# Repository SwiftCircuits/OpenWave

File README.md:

# OpenWave: Precision Arbitrary Waveform Generator

<div align="center">

**A dual-channel, high-precision waveform generator designed for control system analysis and system identification**

[Features](#features) • [Getting Started](#getting-started) • [Documentation](#documentation) • [Contributing](#contributing)

</div>

## Why OpenWave?

Traditional arbitrary waveform generators often force a choice between expensive lab equipment or limited-capability hobby projects. OpenWave bridges this gap by providing professional-grade precision in an open-source design that prioritizes signal quality over raw speed. By focusing on the critical frequency range used in control systems and system identification (up to 500 kHz), we've optimized for exceptional signal quality and reliability.

### Key Features

- Dual independent channels with 16-bit resolution
- Optimized 500 kHz bandwidth with 80 dB SNR
- Sophisticated triggering system for precise control
- Multiple interface options: USB, Ethernet, and CAN
- Intuitive front panel control with LCD display
- Expansion capability through daughter board interface
- Precision temperature-monitored reference system
- Professional-grade signal filtering and conditioning

### Perfect For

- Control system development and testing
- System identification experiments
- Precision measurement applications
- Educational laboratory setups
- Research and development projects
- Industrial control system integration
- Signal processing development

## Technical Overview

OpenWave combines meticulous hardware design with flexible software to achieve exceptional signal quality:

### Signal Generation
- Dual 16-bit DACs (LTC2642-16) operating at 50 MSPS
- Third-order Sallen-Key filtering with Butterworth response
- Additional output stage conditioning
- Ultra-low noise power supply design
- Temperature-compensated reference system
- Comprehensive signal isolation and protection

### Control and Interface
- High-speed USB 2.0 interface
- 10/100 Ethernet connectivity
- Industrial-grade CAN interface
- Advanced trigger system with multiple modes:
  - Start trigger with precise timing
  - Level-sensitive pause control
  - Configurable burst mode
  - Status and peak detection outputs
- Intuitive front panel interface with LCD display

### Power System
- 12V DC input with protection
- Sophisticated multi-stage power architecture:
  - High-efficiency 5.5V pre-regulation
  - Ultra-low noise 5V analog supply
  - Clean 3.3V digital rail
  - Precision 3.3V reference
- Extensive power filtering and isolation

## Getting Started

### Current Status
This project is under active development. Current focus areas:
- Finalizing PCB layout and power distribution
- Implementing core firmware features
- Developing user interface systems
- Creating comprehensive documentation
- Establishing test procedures

### For Contributors

We welcome contributions in several areas:

**Hardware Development**
- PCB layout optimization
- Signal integrity improvements
- Power distribution refinement
- Manufacturing optimization
- Test coverage enhancement

**Firmware Development**
- STM32 core implementation
- Front panel interface development
- Communication protocol implementation
- Signal generation algorithms
- User interface refinement

**Documentation and Testing**
- System specification documentation
- Assembly and calibration procedures
- Performance verification methods
- Application examples
- User manual development

## Building OpenWave

### Hardware Requirements
- 4-layer PCB manufacturing capability
- SMD assembly equipment
- Precision test equipment:
  - Oscilloscope (>100MHz bandwidth)
  - Precision multimeter
  - Signal analyzer (recommended)
- STM32 programming capability
- Basic electronic assembly tools

### Software Requirements
- STM32CubeIDE development environment
- ARM GCC toolchain
- KiCad 7.0 or later
- Git version control
- Build system requirements (detailed in documentation)

## Documentation

> 🚧 Documentation is currently under development

Comprehensive documentation will cover:
- Complete system architecture
- Detailed theory of operation
- Assembly and testing procedures
- Calibration methodology
- Performance optimization
- Application examples
- Development guidelines

## Contributing

Your expertise can help make OpenWave better! Here's how you can contribute:

1. **Join Discussions**
   - Share your application requirements
   - Suggest performance improvements
   - Help define future features
   - Participate in design reviews

2. **Technical Contributions**
   - PCB design optimization
   - Firmware development
   - Documentation creation
   - Test procedure development
   - Performance validation

3. **Testing and Validation**
   - Prototype building and testing
   - Performance verification
   - Use case validation
   - Issue reporting and tracking

## Project Structure

```
/hardware           - KiCad design files
  /main            - Main board design
  /front_panel     - Front panel PCB
  /daughter_boards - Expansion board designs
  /manufacturing   - Production files
/firmware          - Source code
  /core            - Core STM32H7 functionality
  /front_panel     - STM32G0 interface code
  /libraries       - Shared libraries
  /tests           - Test suites
/docs              - Documentation
  /hardware        - Hardware documentation
  /firmware        - Software documentation
  /user            - User guides
  /testing         - Test procedures
```

## License

- Hardware: [CERN Open Hardware License Version 2](LICENSE-HARDWARE)
- Software: [MIT License](LICENSE-SOFTWARE)

## Acknowledgments

OpenWave builds on the work of many open-source projects and individuals. Special thanks to:
- The open hardware community for inspiration and shared knowledge
- Contributors who have helped shape the project's direction

## Contact and Support

- Create an issue for bugs or feature requests
- Join our discussions for general questions
- Email for other inquiries: constantinescu.alex02@gmail.com

---

<div align="center">

**[Back to Top](#openwave-precision-arbitrary-waveform-generator)**

</div>

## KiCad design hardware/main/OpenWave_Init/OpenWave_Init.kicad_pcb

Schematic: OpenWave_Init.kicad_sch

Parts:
BT1: Battery_Cell; Battery_Panasonic_CR1220-VCN_Vertical_CircularHoles
C1, C16, C19, C28: 1uF; C_0402; Voltage Rated 25V; Tolerance ±10%; Part CL05A105KA5NQNC; LCSC C52923
C2, C3, C4, C5, C6, C11, C15, C27, C29, C30, C31, C37, C38, C48, C55, C56, C57, C58, C59: 100nF; C_0402; Voltage Rated 50V; Tolerance ±10%; Part CL05B104KB54PNC; LCSC C307331
C7, C34: 10uF; C_CASE-A-3216-18(mm); Tolerance ±10%; Rated Voltage 16V; Part TAJA106K016RNJ; LCSC C7171
C8, C9: 10pF; C_0402; Voltage Rated 50V; Tolerance ±5%; Part CL05C100JB5NNNC; LCSC C32949
C10, C36: 2.2uF; C_0603; Voltage Rated 16V; Tolerance ±10%; Part CL10A225KO8NNNC; LCSC C23630
C12, C13, C14, C20, C35, C39, C54, C62: 10uF; C_0603; Voltage Rated 25V; Tolerance ±20%; Part CL10A106MA8NRNC; LCSC C96446
C17, C18, C21: 22uF; C_0805; Voltage Rated 25V; Tolerance ±20%; Part CL21A226MAQNNNE; LCSC C45783
C22, C23, C64: 4.7uF; C_0603; Voltage Rated 16V; Tolerance ±10%; Part CL10A475KO8NNNC; LCSC C19666
C24, C25, C26, C42, C46: 100pF; C_0402; Voltage Rated 50V; Tolerance ±5%; Part 0402CG101J500NT; LCSC C1546
C32, C33, C51, C63: 10nF; C_0402; Voltage Rated 50V; Tolerance ±10%; Part CL05B103KB5NNNC; LCSC C15195
C40, C47: 220nF; C_0402; Voltage Rated 16V; Tolerance ±10%; Part CL05B224KO5NNNC; LCSC C16772
C41, C45: 1.5nF; C_0603; Voltage Rated 50V; Tolerance ±10%; Part 0603B152K500NT; LCSC C1595
C43, C44: 680pF; C_0402; Voltage Rated 50V; Tolerance ±5%; Part 0402CG101J500NT
C49, C50: 6.8pF; C_0402; Voltage Rated 50V; Part 0402CG6R8C500NT; LCSC C1576
C52, C53: 15pF; C_0402; Voltage Rated 50V; Tolerance ±5%; Part 0402CG150J500NT; LCSC C1548
D1: LED; LED_0603_1608Metric
D2: SMAJ10CA; D_SMA; Part SMAJ10CA; LCSC C19077530
D3, D4, D5, D6, D7: TPRCLAMP2451ZA; D_DFN0603-2; Part TPRCLAMP2451ZA; LCSC C2936988
FB1, FB2, FB3, FB4, FB5, FB7: FB_0603; Current Rating 200mA; Tolerance ±25%; Part GZ1608D601TF; LCSC C1002
FB6: FB_0805; Current Rating 800mA; Tolerance ±25%; Part GZ2012D101TF; LCSC C1015
FL1: ACT1210D-101-2P-TL00; ACT1210D1012PTL00
FL2: Choke_Coilcraft_0603USB-222; L_CommonModeChoke_Coilcraft_0603USB
H1, H2, H3, H4: Hole, 3mm
IC1: TPS7A2050PDBVR; SOT95P280X145-5N; Mouser Part Number 595-TPS7A2050PDBVR
J1: UART; PinHeader_1x02_P2.54mm_Vertical
J2: SWD; PinHeader_2x03_P1.00mm_Vertical
J3: FPC 6S; Hirose_FH12-6S-0.5SH_1x06-1MP_P0.50mm_Horizontal
J4: Barrel_Jack_Switch_MountingPin; PRT10811
J5: Control_In; JST_XH_S2B-XH-A-1_1x02_P2.50mm_Horizontal
J6, J7: BNC; 5415025-2
J8: USB_C_Receptacle_USB2.0_16P; USB_C_Receptacle_GCT_USB4105-xx-A_16P_TopMnt_Horizontal
J9: RB1-125BAG1A; RB1125BAG1A; Mouser Part Number 950-RB1-125BAG1A
JP1: SolderJumper; SolderJumper-2_P1.3mm_Bridged2Bar_Pad1.0x1.5mm
JP2: Termination Jumper; SolderJumper-2_P1.3mm_Open_Pad1.0x1.5mm
L1: 22uH, 340mA; L_1210_3225Metric; Part SRN2012T-220K; LCSC DNP
PN1: Part_Num_JLCPCB
R1, R13, R14, R17: 10kΩ; R_0402; Overload Voltage (Max) 50V; Tolerance ±1%; Part 0402WGF1002TCE; LCSC C25744
R2: 1.5kΩ; R_0402; Overload Voltage (Max) 50V; Tolerance ±1%; Part 0402WGF1501TCE; LCSC C25867
R3: 3.3kΩ; R_0402; Overload Voltage (Max) 50V; Tolerance ±1%; Part 0402WGF3301TCE; LCSC C25890
R4, R42: 330Ω; R_0402; Overload Voltage (Max) 50V; Tolerance ±1%; Part 0402WGF3300TCE; LCSC C25104
R5, R6, R10: 4.7kΩ; R_0402; Overload Voltage (Max) 50V; Tolerance ±1%; Part 0402WGF4701TCE; LCSC C25900
R7: 240kΩ; R_0603; Overload Voltage (Max) 75V; Tolerance ±1%; Part 0603WAF2403T5E; LCSC C4197
R8: 150kΩ; R_0402; Overload Voltage (Max) 50V; Tolerance ±1%; Part 0402WGF1503TCE; LCSC C25755
R9: 30kΩ; R_0603; Overload Voltage (Max) 75V; Tolerance ±1%; Part 0603WAF3002T5E; LCSC C22984
R11: 100kΩ; R_0402; Overload Voltage (Max) 50V; Tolerance ±1%; Part 0402WGF1003TCE; LCSC C25741
R12, R26, R29: 120Ω; R_0402; Overload Voltage (Max) 50V; Tolerance ±1%; Part 0402WGF1200TCE; LCSC C25079
R15, R16: 5.1kΩ; R_0402; Overload Voltage (Max) 50V; Tolerance ±1%; Part 0402WGF5101TCE; LCSC C25905
R18: 100Ω; R_0603; Overload Voltage (Max) 75V; Tolerance ±1%; Part 0603WAF1000T5E; LCSC C22775
R19, R20: 33Ω; R_0402; Overload Voltage (Max) 50V; Tolerance ±1%; Part 0402WGF330JTCE; LCSC C25105
R21, R22, R23, R24, R33, R34, R38, R39: 49.9Ω; R_0402; Overload Voltage (Max) 50V; Tolerance ±1%; Part 0402WGF499JTCE; LCSC C25120
R25, R32: 1Ω; R_0402; Overload Voltage (Max) 50V; Tolerance ±1%; Part 0402WGF100KTCE; LCSC C25086
R27, R30: 1.2kΩ; R_0402; Overload Voltage (Max) 50V; Tolerance ±1%; Part 0402WGF1201TCE; LCSC C25862
R28, R31: 360Ω; R_0603; Overload Voltage (Max) 75V; Tolerance ±1%; Part 0603WAF3600T5E; LCSC C25194
R35: 10Ω; R_0402; Overload Voltage (Max) 50V; Tolerance ±1%; Part 0402WGF100JTCE; LCSC C25077
R36, R37: 220Ω; R_0402; Overload Voltage (Max) 50V; Tolerance ±1%; Part 0402WGF2200TCE; LCSC C25091
R40: 1MΩ; R_0402; Overload Voltage (Max) 50V; Tolerance ±1%; Part 0402WGF1004TCE; LCSC C26083
R41: 12kΩ; R_0402; Overload Voltage (Max) 50V; Tolerance ±1%; Part 0402WGF1202TCE; LCSC C25752
R43: 75Ω; R_0402; Overload Voltage (Max) 50V; Tolerance ±1%; Part 0402WGF750JTCE; LCSC C25133
U1: STM32H743VITx; LQFP-100_14x14mm_P0.5mm
U2: AP7363-33D-13; DPAK-3_L6.6-W6.1-P2.28-LS9.9-BR; LCSC Part C108723
U3: TPSM863257RDXR; QFN-7_L4.0-W3.3_TPSM863257RDXR; LCSC Part C19190416
U4: REF3333AIDBZR; SOT-23-3_L2.9-W1.6-P1.90-LS2.8-BR; LCSC Part C130016
U5: TJA1051T-3; SOIC-8_3.9x4.9mm_P1.27mm
U6, U8: LTC2642IMS-16#PBF; MSOP-10_L3.0-W3.0-P0.50-LS4.9-BL; LCSC Part C580595
U7: LMH6658MAX_NOPB; SOIC127P600X175-8N; Mouser Part Number 926-LMH6658MAX/NOPB
U9, U10: TMP100; SOT-23-6
U11: USBLC6-2P6; SOT-666
U12: W25Q128; SOIC-8_L5.3-W5.3-P1.27-LS8.0-BL; Part W25Q128JVSIQ; LCSC C97521
U13: SN74LVC8T245; VQFN-24_L5.6-W3.6-P0.50-BL-EP
U14: W5500; LQFP-48_7x7mm_P0.5mm
X1, X2: X322525MOB4SI; OSC-SMD_4P-L3.2-W2.5-BL; Frequency Tolerance ±10ppm; Part X322525MOB4SI; LCSC C9006

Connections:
+3.3VA_uC: C1.1, C2.1, FB1.2, U1.20 (VREF+), U1.21 (VDDA)
+3.3VDAC: C22.1, C27.2, C28.2, C29.2, R13.1, R14.1, U4.2 (OUT), U6.1 (REF), U6.7 (INV), U6.8 (RFB), U8.1 (REF), U8.7 (INV), U8.8 (RFB)
+3V3: C3.1, C4.1, C5.1, C6.1, C7.1, C13.1, C26.1, C32.1, C33.1, C37.1, C39.1, C54.1, C55.1, D7.2, FB1.1, FB7.1, J2.1, J3.1, J9.L1 (A_YELLOW), J9.L3 (A_GREEN), JP1.1 (A), R33.1, R34.1, R35.1, U1.11 (VDD), U1.27 (VDD), U1.50 (VDD), U1.75 (VDD), U1.100 (VDD), U2.3 (OUT), U5.5 (VIO), U9.4 (V+), U10.4 (V+), U10.5 (ADD0), U12.8 (VCC), U13.1 (V_{CCA}), U14.28 (VDD)
+5.5V: C12.1, C17.1, C18.1, C23.1, R7.2, R18.1, U2.1 (IN), U3.3 (VOUT), U4.1 (IN), U5.3 (VCC)
+5VA: C21.1, FB3.1, FB4.1, FB5.1, L1.2, U13.23 (V_{CCB}), U13.24 (V_{CCB})
+5V_USB: J8.A4 (VBUS), J8.A9 (VBUS), J8.B4 (VBUS), J8.B9 (VBUS), R2.2, U11.5 (VBUS)
+12V: C14.1, C15.1, C35.1, FB6.2, R8.1, U3.1 (VIN)
/ACT_LED: R37.1, U14.27 (ACTLED)
/LINK_LED: R36.1, U14.25 (LINKLED)
/uC_SW_CLK: R22.2, U1.76 (PA14)
/uC_SW_DIO: R23.2, U1.72 (PA13)
/uC_SW_NRST: R24.2, U1.14 (NRST)
/uC_SW_O: R21.2, U1.89 (PB3)
/uC_USB_VBUS: R2.1, R3.1, U1.68 (PA9)
/uc_QSPI_CLK: U1.36 (PB2), U12.6 (CLK)
/uc_QSPI_CS: U1.46 (PB10), U12.1 (CS#)
/uc_QSPI_IO0: U1.58 (PD11), U12.5 (DI)
/uc_QSPI_IO1: U1.59 (PD12), U12.2 (DO)
/uc_QSPI_IO2: U1.1 (PE2), U12.3 (IO2)
/uc_QSPI_IO3: U1.60 (PD13), U12.7 (IO3)
CAN_H: C24.1, FL1.1, JP2.2 (B), U5.7 (CANH)
CAN_L: C25.2, FL1.2, R12.2, U5.6 (CANL)
DAC_SPI2_CLK: U6.3 (SCLK), U13.15 (B7)
DAC_SPI2_CS: U6.2 (~CS), U13.16 (B6)
DAC_SPI2_MOSI: U6.4 (DIN), U13.14 (B8)
DAC_SPI_CLK: U8.3 (SCLK), U13.20 (B2)
DAC_SPI_CS: U8.2 (~CS), U13.21 (B1)
DAC_SPI_MOSI: U8.4 (DIN), U13.19 (B3)
GND: BT1.2 (-), C1.2, C2.2, C3.2, C4.2, C5.2, C6.2, C7.2, C8.1, C9.2, C10.1, C11.1, C12.2, C13.2, C14.2, C15.2, C16.2, C17.2, C18.2, C19.2, C20.2, C21.2, C22.2, C23.2, C24.2, C25.1, C26.2, C27.1, C28.1, C29.1, C30.2, C31.2, C32.2, C33.2, C34.2, C35.2, C36.1, C37.2, C38.2, C39.2, C40.2, C41.2, C42.2, C45.2, C46.2, C47.2, C48.2, C51.2, C52.1, C53.2, C54.2, C55.2, C56.2, C57.2, C58.2, C59.2, C62.2, C63.2, C64.2, D1.1, D2.2, D3.1, D4.1, D5.1, D6.1, D7.1, H1.1, H2.1, H3.1, H4.1, IC1.2 (GND), J2.5, J3.6, J3.MP (MountPin), J4.2, J4.MP (MountPin), J6.2 (Ext), J7.2 (Ext), J8.A1 (GND), J8.A12 (GND), J8.B1 (GND), J8.B12 (GND), J8.S1 (SHIELD), J9.1 (SHIELD_1), J9.2 (SHIELD_2), R3.2, R9.2, R11.2, R15.1, R16.1, R17.2, R43.2, U1.10 (VSS), U1.19 (VSSA), U1.26 (VSS), U1.49 (VSS), U1.74 (VSS), U1.99 (VSS), U2.2 (GND), U3.4 (PGND), U4.3 (GND), U5.2 (GND), U6.10 (GND), U7.4 (V_-), U8.10 (GND), U9.2 (GND), U9.3 (ADD1), U9.5 (ADD0), U10.2 (GND), U10.3 (ADD1), U11.2 (GND), U12.4 (GND), U13.11 (GND), U13.12 (GND), U13.13 (GND), U14.3 (AGND), U14.9 (AGND), U14.14 (AGND), U14.16 (AGND), U14.19 (AGND), U14.29 (GND), U14.48 (AGND), X1.2 (GND), X1.4 (GND), X2.2 (GND), X2.4 (GND)
LLT_DIR: U13.2 (DIR)
LLT_OE: U13.22 (~OE)
unnamed: BT1.1 (+), C38.1, JP1.2 (B), U1.6 (VBAT)
unnamed: C10.2, U1.73 (VCAP)
unnamed: C20.1, FB2.2, L1.1
unnamed: C36.2, U1.48 (VCAP)
unnamed: C41.1, R26.2, R27.1
unnamed: C43.1, R27.2, R28.1
unnamed: C44.1, R30.2, R31.1
unnamed: C45.1, R29.2, R30.1
unnamed: C51.1, R38.2, R39.2
unnamed: C56.1, C57.1, C58.1, C59.1, C62.1, FB7.2, U14.4 (AVDD), U14.8 (AVDD), U14.11 (AVDD), U14.15 (AVDD), U14.17 (AVDD), U14.21 (AVDD)
unnamed: D1.2, R4.2
unnamed: D2.1, FB6.1, J4.1
unnamed: FL2.1, U11.4 (I/O2)
unnamed: FL2.4, U11.6 (I/O1)
unnamed: IC1.3 (EN), R10.1
unnamed: C16.1, C34.1, IC1.1 (IN), R10.2, R18.2
unnamed: C19.1, FB2.1, IC1.5 (OUT)
unnamed: D5.2, J2.2, R23.1
unnamed: C11.2, D6.2, J2.3, R24.1
unnamed: D4.2, J2.4, R22.1
unnamed: D3.2, J2.6, R21.1
unnamed: FL1.3, J5.1
unnamed: FL1.4, J5.2
unnamed: C40.1, J6.1 (In), R25.2
unnamed: C47.1, J7.1 (In), R32.2
unnamed: J8.A5 (CC1), R15.2
unnamed: J8.B5 (CC2), R16.2
unnamed: J8.A6 (D+), J8.B6 (D+), U11.3 (I/O2)
unnamed: J8.A7 (D-), J8.B7 (D-), U11.1 (I/O1)
unnamed: J8.A8 (SBU1), J8.B8 (SBU2), R17.1
unnamed: C48.1, J9.R3 (CT), R35.2
unnamed: J9.L4 (K_GREEN), R37.2
unnamed: J9.L2 (K_YELLOW), R36.2
unnamed: C49.2, J9.R7 (RD+)
unnamed: C50.2, J9.R8 (RD-)
unnamed: J9.R1 (TD+), R33.2, U14.2 (TXP)
unnamed: J9.R2 (TD-), R34.2, U14.1 (TXN)
unnamed: JP2.1 (A), R12.1
unnamed: R41.2, R42.1
unnamed: R42.2, R43.1
unnamed: R1.2, U1.94 (BOOT0)
unnamed: R20.2, U1.29 (PA5)
unnamed: R19.2, U1.42 (PE12)
unnamed: C8.2, U1.12 (PH0), X1.3 (OSC)
unnamed: C9.1, U1.13 (PH1), X1.1 (OSC)
unnamed: R8.2, R11.1, U3.6 (EN)
unnamed: R7.1, R9.1, U3.7 (FB)
unnamed: C30.1, FB4.2, U6.9 (VDD)
unnamed: R26.1, U6.6 (VOUT)
unnamed: R13.2, U6.5 (~CLR)
unnamed: C42.1, R28.2, U7.3 (+IN_A)
unnamed: C46.1, R31.2, U7.5 (+IN_B)
unnamed: FB3.2, U7.8 (V_+)
unnamed: C31.1, FB5.2, U8.9 (VDD)
unnamed: R29.1, U8.6 (VOUT)
unnamed: R14.2, U8.5 (~CLR)
unnamed: C63.1, U14.22 (1V2O)
unnamed: R41.1, U14.10 (EXRES1)
unnamed: C50.1, R39.1, U14.5 (RXN)
unnamed: C49.1, R38.1, U14.6 (RXP)
unnamed: C64.1, U14.20 (TOCAP)
unnamed: C52.2, R40.1, U14.30 (XI/CLKIN), X2.3 (OSC)
unnamed: C53.1, R40.2, U14.31 (XO), X2.1 (OSC)
W55_INT: U14.36 (~INT)
W55_RST: U14.37 (~RST)
W55_SPI2_CS: U1.96 (PB9), U14.32 (~SCS)
W55_SPI2_MISO: U1.16 (PC1), U14.34 (MISO)
W55_SPI2_MOSI: U1.17 (PC2_C), U14.35 (MOSI)
W55_SPI2_SCK: U1.84 (PD3), U14.33 (SCLK)
Wave_OUTA: C43.2, R25.1, U7.1 (OUT_A), U7.2 (-IN_A)
Wave_OUTB: C44.2, R32.1, U7.6 (-IN_B), U7.7 (OUT_B)
uC_BOOT0: R1.1
uC_CAN_RX: U1.81 (PD0), U5.4 (RXD)
uC_CAN_SILENT: U5.8 (S)
uC_CAN_TX: U1.82 (PD1), U5.1 (TXD)
uC_I2C_SCL: R6.2, U9.1 (SCL), U10.1 (SCL)
uC_I2C_SDA: R5.2, U9.6 (SDA), U10.6 (SDA)
uC_SPI2_CLK: R20.1, U13.9 (A7)
uC_SPI2_CS: U1.28 (PA4), U13.8 (A6)
uC_SPI2_MOSI: U1.31 (PA7), U13.10 (A8)
uC_SPI3_CLK: J3.3, U1.78 (PC10)
uC_SPI3_CS: J3.2, U1.77 (PA15)
uC_SPI3_MISO: J3.4, U1.79 (PC11)
uC_SPI3_MOSI: J3.5, U1.80 (PC12)
uC_SPI_CLK: R19.1, U13.4 (A2)
uC_SPI_CS: U1.41 (PE11), U13.3 (A1)
uC_SPI_MOSI: U1.44 (PE14), U13.5 (A3)
uC_UART_RX: J1.1
uC_UART_TX: J1.2
uC_USB_D+: FL2.2, U1.71 (PA12)
uC_USB_D-: FL2.3, U1.70 (PA11)

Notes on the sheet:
SPI Mode 0 (CPOL = CPHA = 0) MSB-First CLK Speed - 50 MHz
CAN-BUS
11 pF Crystal 5-7 pF stray from STM
15W
Digital Voltage
POWER
Temp.
Close to Connector
fc = 906 , 916 kHz ζ = 0.49 f = 795 kHz
General Voltage
11 pf Crystal 7.5 pf caps 3-4 pf stray
1001010
Memory
Logic Level 5-3.3
Analog Voltage
fc = 725-800kHz
check 100ohm diff imp
1001000
System VIN
UI Board Conn
USB
Do not ask. =12.4k
10kHz Cut-Off
DAC, OPAMP
Reference Voltage

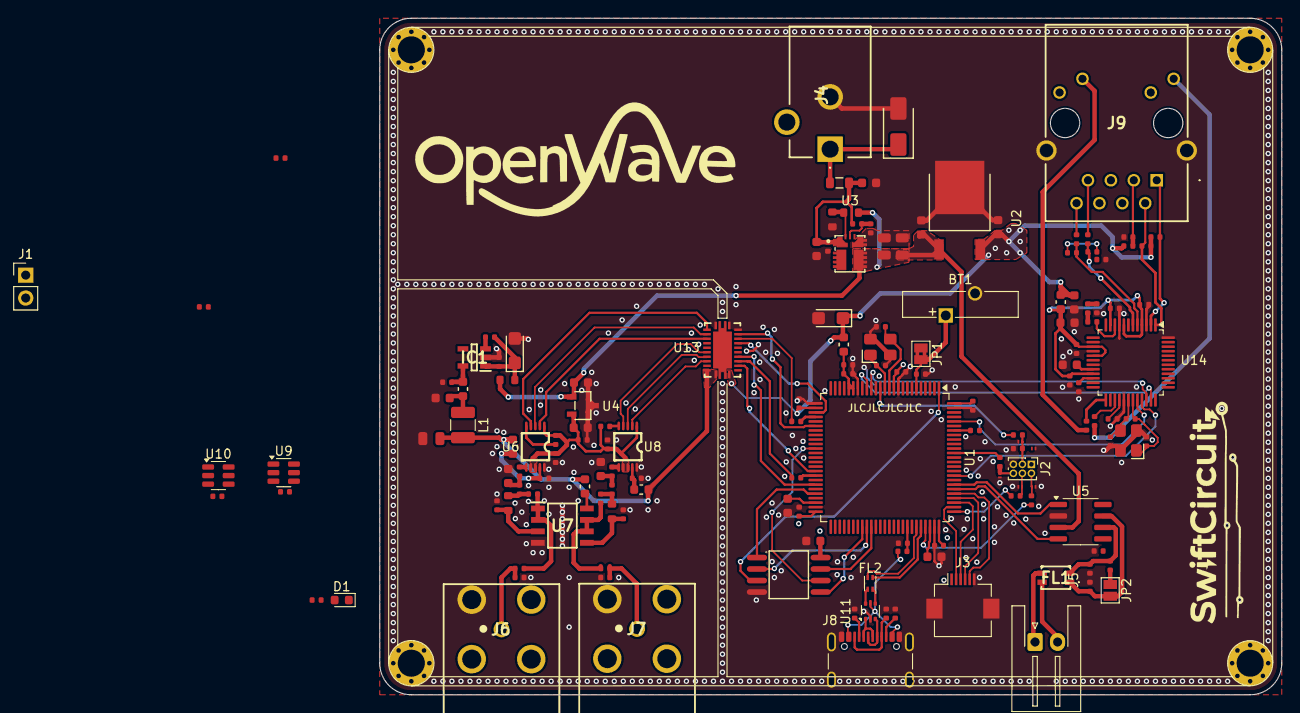
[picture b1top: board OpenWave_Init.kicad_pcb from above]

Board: 4 copper layers, 100.0 x 75.0 mm, 156 parts (0 on the bottom side), 114 nets.

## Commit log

2025-02-18 init
2025-02-19 Logo
2025-02-19 Schematic, Design Changes
2025-02-23 V0.2
2025-02-24 WA5500 implementation
2025-02-24 fixed ethernet, impedance, new swiftcircuit logo, arranged schematic

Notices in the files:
README.md:
License: CERN-OHL
License: MIT
